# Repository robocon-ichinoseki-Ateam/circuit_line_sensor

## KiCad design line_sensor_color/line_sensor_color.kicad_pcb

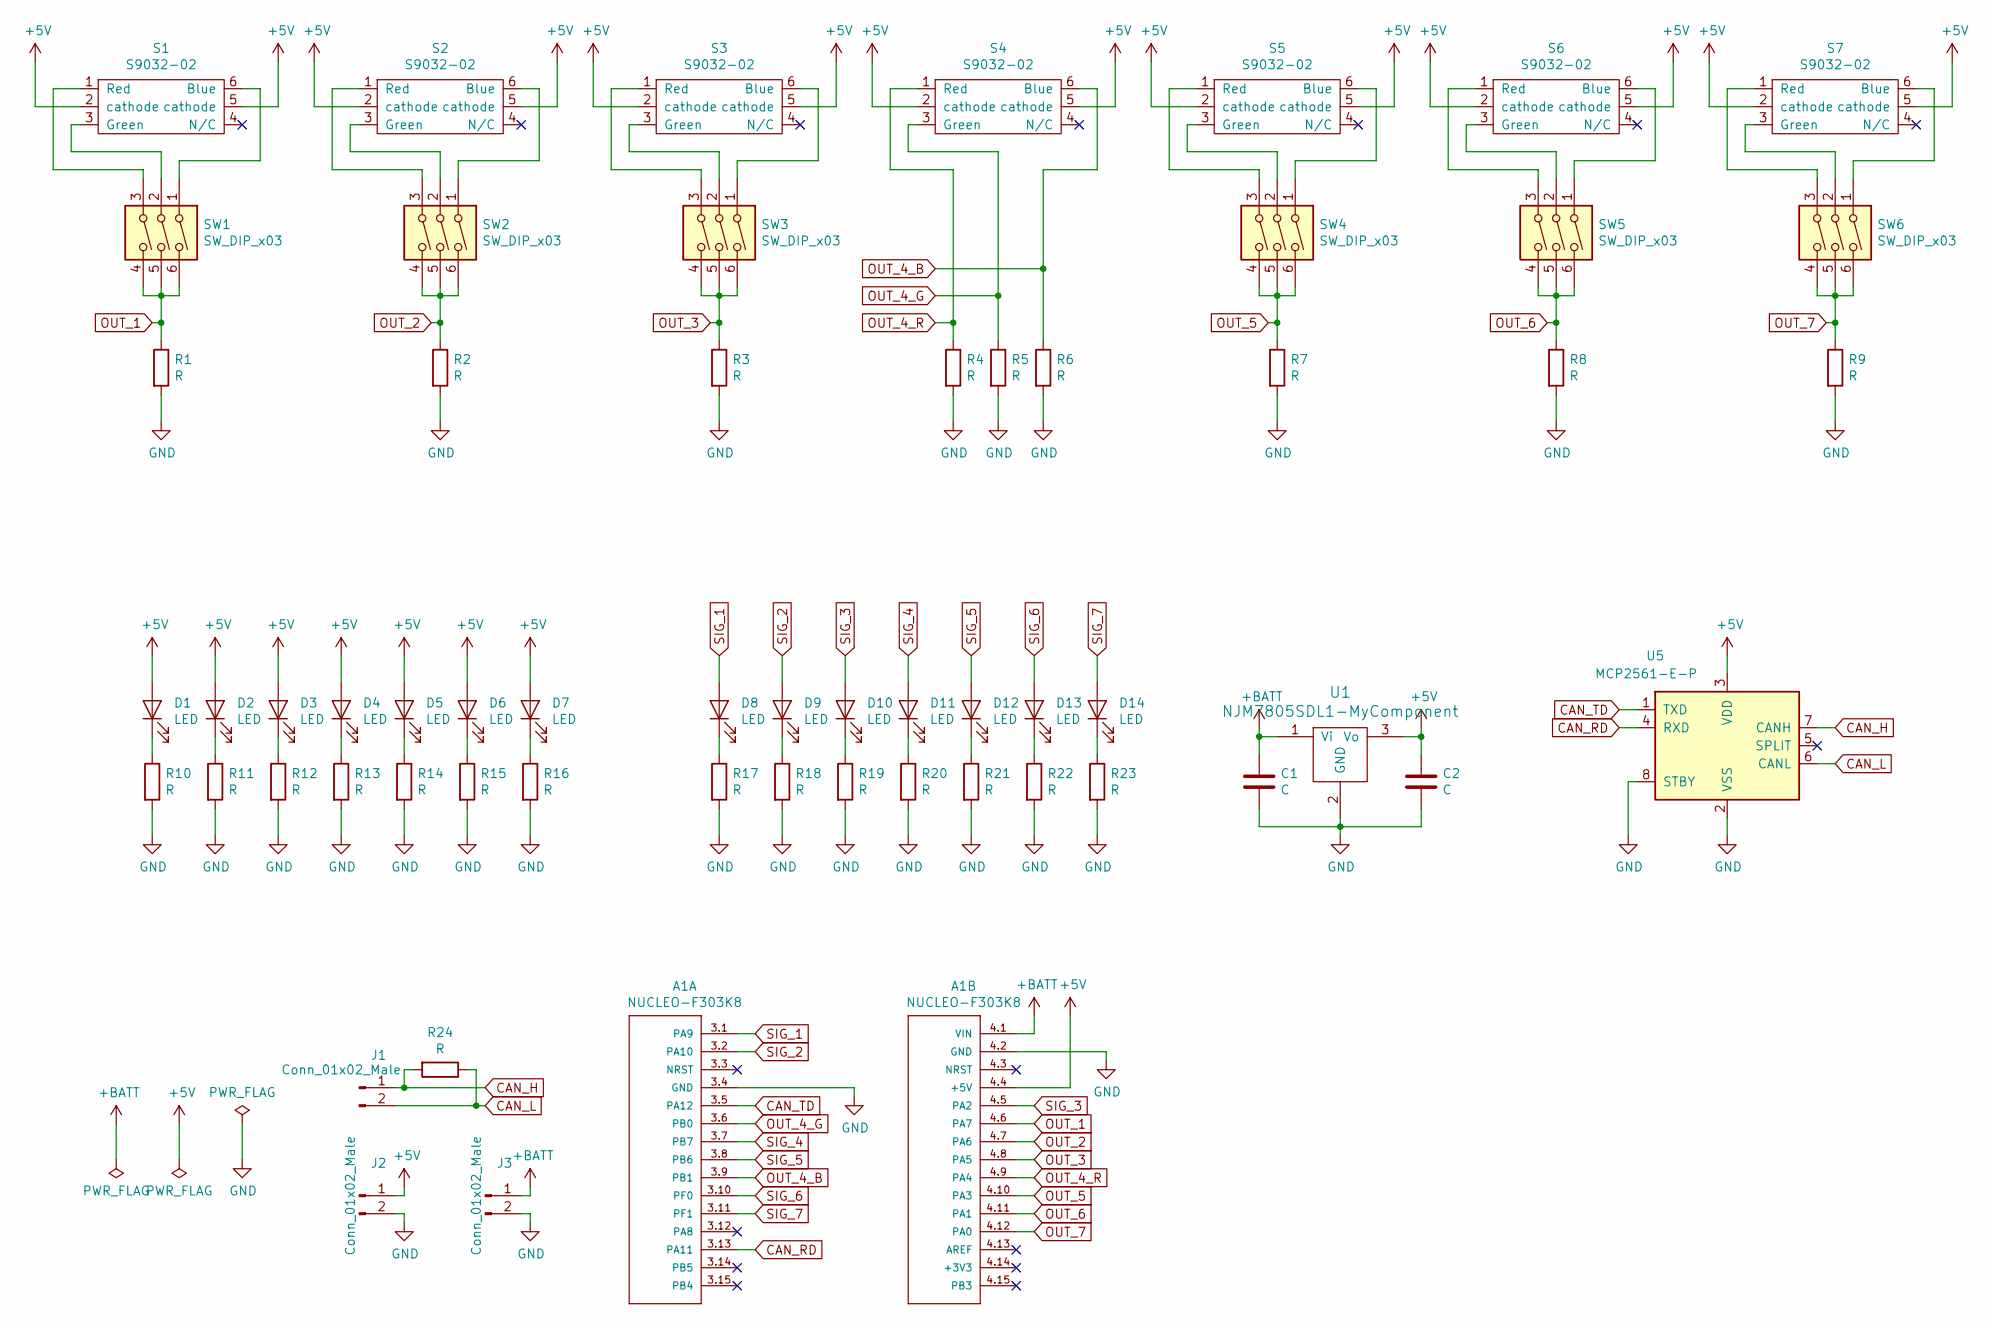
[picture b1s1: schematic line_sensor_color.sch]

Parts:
A1: NUCLEO-F303K8; NUCLEO_F303K8
C1, C2: C; C_0603_1608Metric_Pad1.05x0.95mm_HandSolder
D1, D2, D3, D4, D5, D6, D7: LED; OSW5DLS1C1A
D8, D9, D10, D11, D12, D13, D14: LED; LED_0603_1608Metric_Pad1.05x0.95mm_HandSolder
J1, J2, J3: Conn_01x02_Male; JST_XH_S2B-XH-A_1x02_P2.50mm_Horizontal
R1, R2, R3, R4, R5, R6, R7, R8, R9, R10, R11, R12, R13, R14, R15, R16, R24: R; R_Axial_DIN0207_L6.3mm_D2.5mm_P7.62mm_Horizontal
R17, R18, R19, R20, R21, R22, R23: R; R_0603_1608Metric_Pad1.05x0.95mm_HandSolder
S1, S2, S3, S4, S5, S6, S7: S9032-02
SW1, SW2, SW3, SW4, SW5, SW6: SW_DIP_x03; SW_DIP_SPSTx03_Slide_6.7x9.18mm_W7.62mm_P2.54mm_LowProfile
U1: NJM7805SDL1-MyComponent; TO-252-3_TabPin2
U5: MCP2561-E-P; DIP-8_W7.62mm

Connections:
+5V: A1.4.4 (+5V), C2.1, D1.2 (A), D2.2 (A), D3.2 (A), D4.2 (A), D5.2 (A), D6.2 (A), D7.2 (A), J2.1, S1.2 (cathode), S1.5 (cathode), S2.2 (cathode), S2.5 (cathode), S3.2 (cathode), S3.5 (cathode), S4.2 (cathode), S4.5 (cathode), S5.2 (cathode), S5.5 (cathode), S6.2 (cathode), S6.5 (cathode), S7.2 (cathode), S7.5 (cathode), U1.3 (Vo), U5.3 (VDD)
+BATT: A1.4.1 (VIN), C1.1, J3.1, U1.1 (Vi)
CAN_H: J1.1, R24.2, U5.7 (CANH)
CAN_L: J1.2, R24.1, U5.6 (CANL)
CAN_RD: A1.3.13 (PA11), U5.4 (RXD)
CAN_TD: A1.3.5 (PA12), U5.1 (TXD)
GND: A1.3.4 (GND), A1.4.2 (GND), C1.2, C2.2, J2.2, J3.2, R1.2, R2.2, R3.2, R4.2, R5.2, R6.2, R7.2, R8.2, R9.2, R10.2, R11.2, R12.2, R13.2, R14.2, R15.2, R16.2, R17.2, R18.2, R19.2, R20.2, R21.2, R22.2, R23.2, U1.2 (GND), U5.2 (VSS), U5.8 (STBY)
unnamed: D1.1 (K), R10.1
unnamed: D2.1 (K), R11.1
unnamed: D3.1 (K), R12.1
unnamed: D4.1 (K), R13.1
unnamed: D5.1 (K), R14.1
unnamed: D6.1 (K), R15.1
unnamed: D7.1 (K), R16.1
unnamed: D8.1 (K), R17.1
unnamed: D9.1 (K), R18.1
unnamed: D10.1 (K), R19.1
unnamed: D11.1 (K), R20.1
unnamed: D12.1 (K), R21.1
unnamed: D13.1 (K), R22.1
unnamed: D14.1 (K), R23.1
unnamed: S1.1 (Red), SW1.3
unnamed: S1.3 (Green), SW1.2
unnamed: S1.6 (Blue), SW1.1
unnamed: S2.1 (Red), SW2.3
unnamed: S2.3 (Green), SW2.2
unnamed: S2.6 (Blue), SW2.1
unnamed: S3.1 (Red), SW3.3
unnamed: S3.3 (Green), SW3.2
unnamed: S3.6 (Blue), SW3.1
unnamed: S5.1 (Red), SW4.3
unnamed: S5.3 (Green), SW4.2
unnamed: S5.6 (Blue), SW4.1
unnamed: S6.1 (Red), SW5.3
unnamed: S6.3 (Green), SW5.2
unnamed: S6.6 (Blue), SW5.1
unnamed: S7.1 (Red), SW6.3
unnamed: S7.3 (Green), SW6.2
unnamed: S7.6 (Blue), SW6.1
OUT_1: A1.4.6 (PA7), R1.1, SW1.4, SW1.5, SW1.6
OUT_2: A1.4.7 (PA6), R2.1, SW2.4, SW2.5, SW2.6
OUT_3: A1.4.8 (PA5), R3.1, SW3.4, SW3.5, SW3.6
OUT_4_B: A1.3.9 (PB1), R6.1, S4.6 (Blue)
OUT_4_G: A1.3.6 (PB0), R5.1, S4.3 (Green)
OUT_4_R: A1.4.9 (PA4), R4.1, S4.1 (Red)
OUT_5: A1.4.10 (PA3), R7.1, SW4.4, SW4.5, SW4.6
OUT_6: A1.4.11 (PA1), R8.1, SW5.4, SW5.5, SW5.6
OUT_7: A1.4.12 (PA0), R9.1, SW6.4, SW6.5, SW6.6
SIG_1: A1.3.1 (PA9), D8.2 (A)
SIG_2: A1.3.2 (PA10), D9.2 (A)
SIG_3: A1.4.5 (PA2), D10.2 (A)
SIG_4: A1.3.7 (PB7), D11.2 (A)
SIG_5: A1.3.8 (PB6), D12.2 (A)
SIG_6: A1.3.10 (PF0), D13.2 (A)
SIG_7: A1.3.11 (PF1), D14.2 (A)

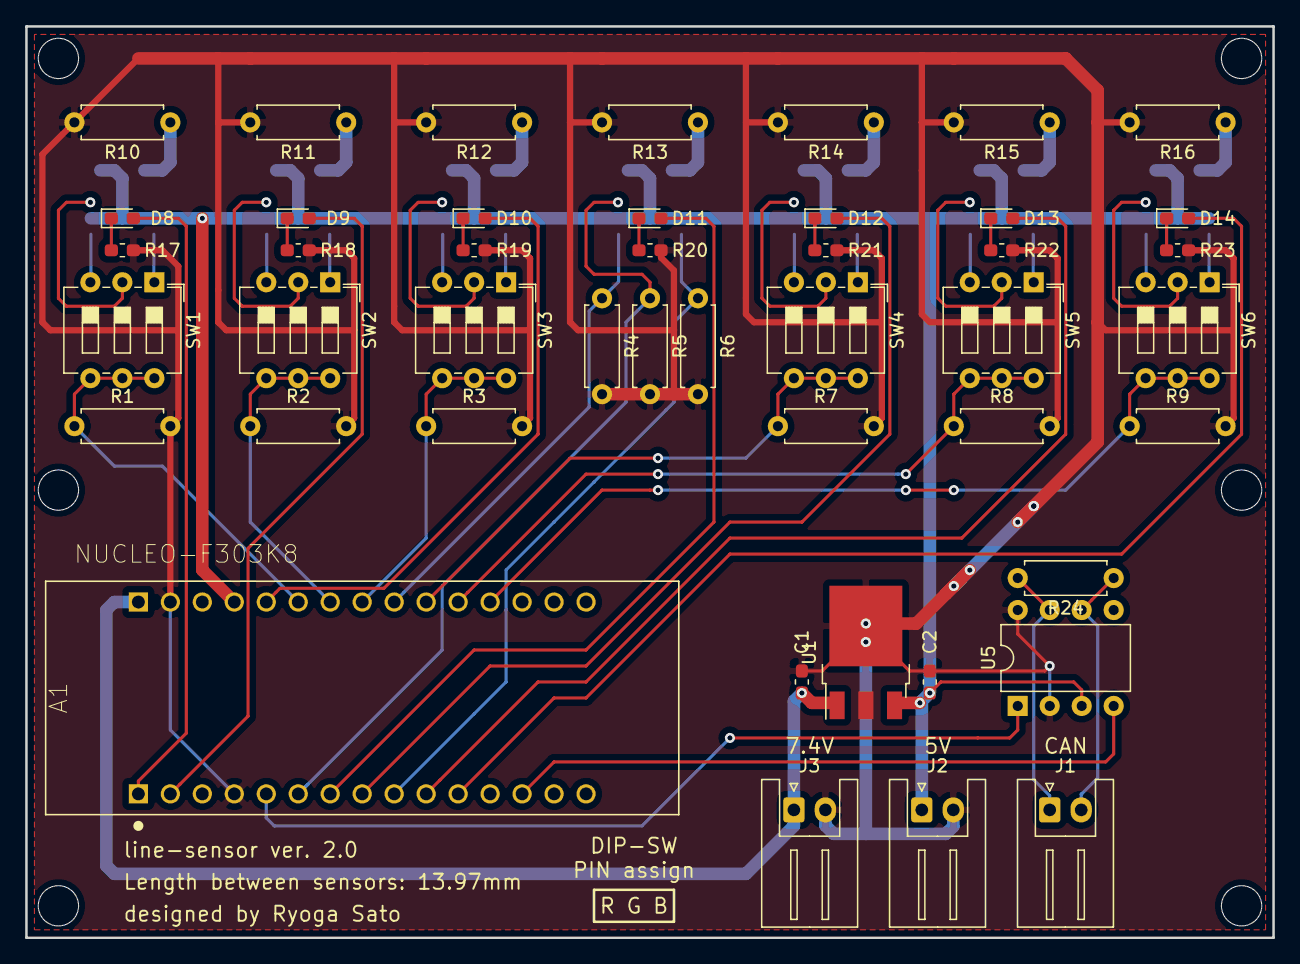
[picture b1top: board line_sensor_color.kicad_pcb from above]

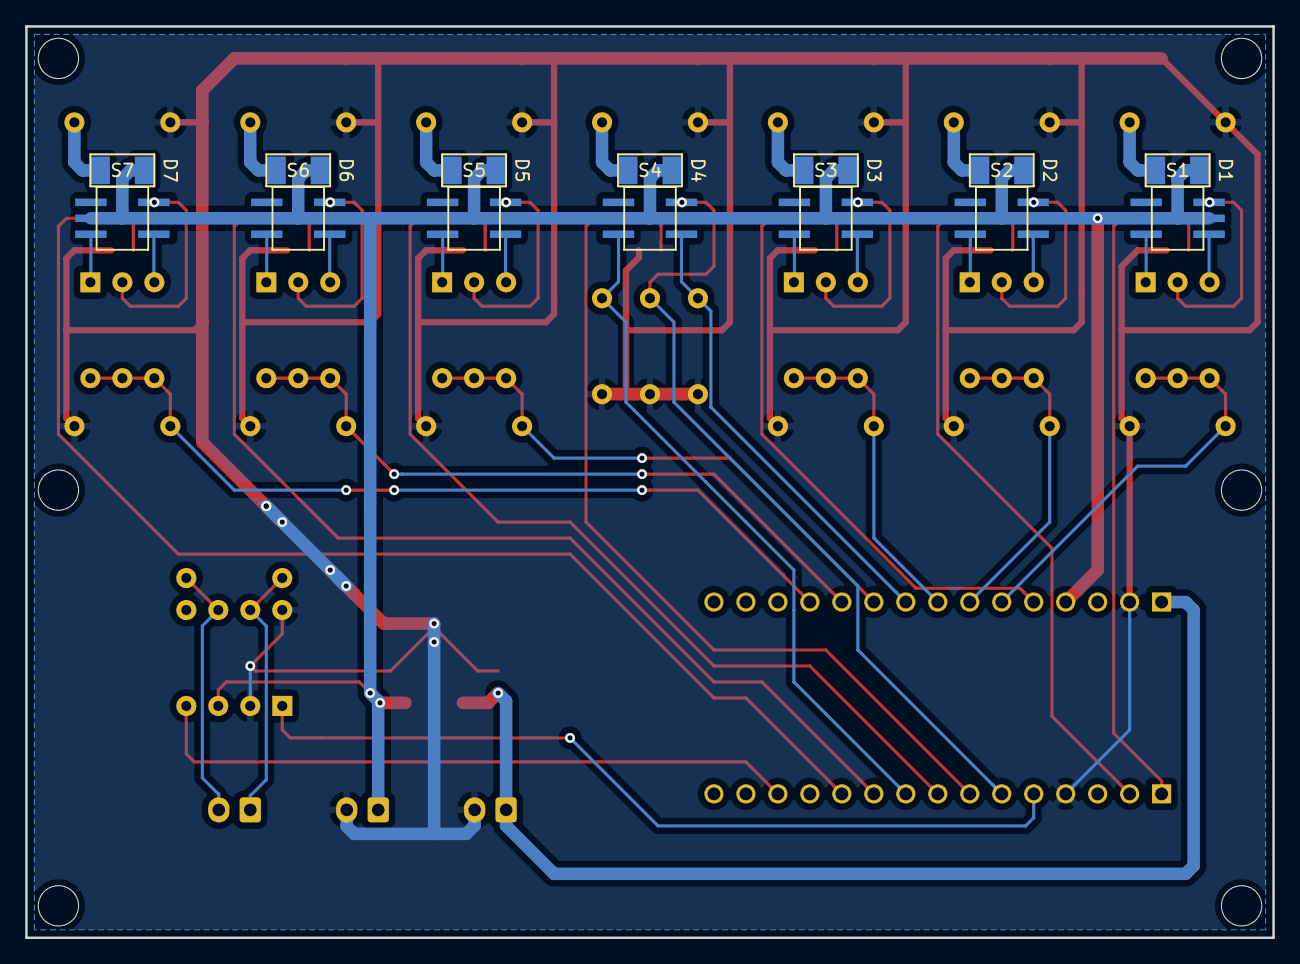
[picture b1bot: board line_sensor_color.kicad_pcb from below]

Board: 2 copper layers, 99.1 x 72.4 mm, 59 parts (14 on the bottom side), 55 nets.

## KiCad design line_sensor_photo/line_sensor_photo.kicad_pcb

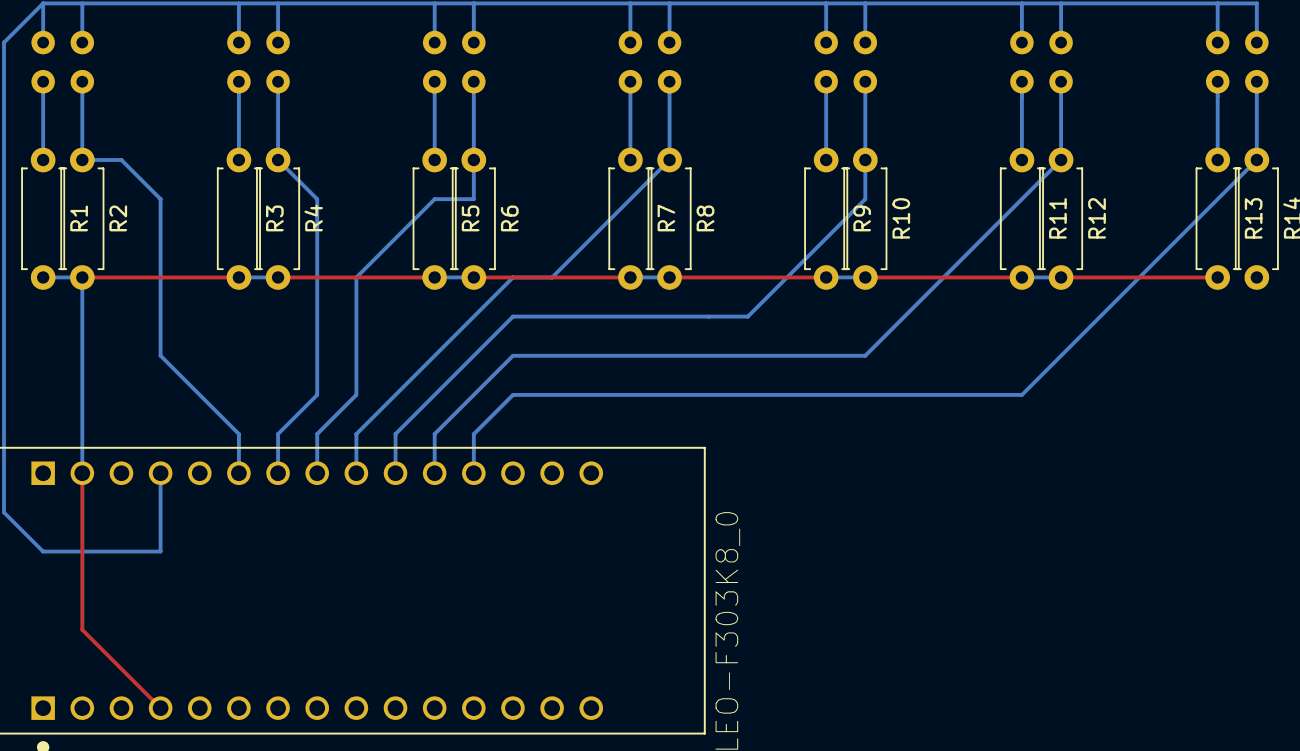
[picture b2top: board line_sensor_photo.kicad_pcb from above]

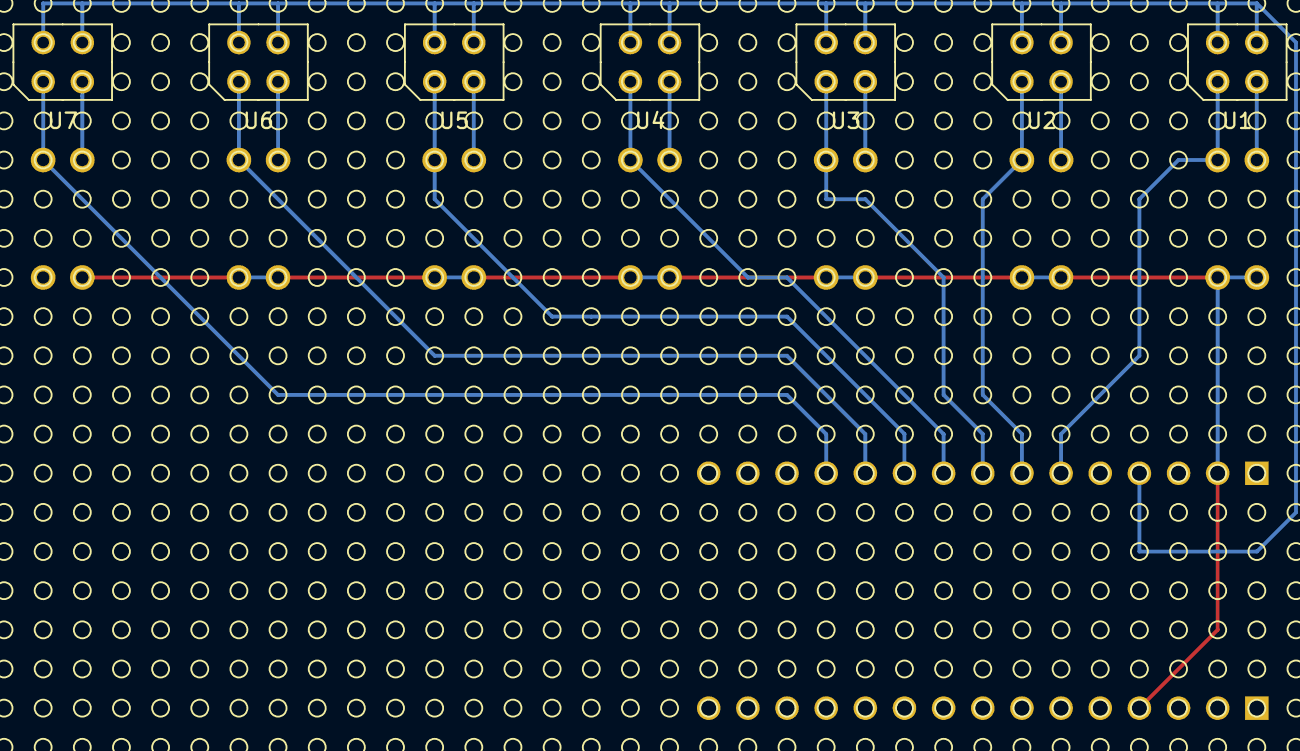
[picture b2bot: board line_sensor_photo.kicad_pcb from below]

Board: 2 copper layers, 22 parts (7 on the bottom side), 16 nets.

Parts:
A1: NUCLEO-F303K8_0; NUCLEO_F303K8
R1, R2, R3, R4, R5, R6, R7, R8, R9, R10, R11, R12, R13, R14: R; R_Axial_DIN0207_L6.3mm_D2.5mm_P7.62mm_Horizontal
U1, U2, U3, U4, U5, U6, U7: RPR-220

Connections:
+5V: A1.4.4, U1.1, U1.4, U2.1, U2.4, U3.1, U3.4, U4.1, U4.4, U5.1, U5.4, U6.1, U6.4, U7.1, U7.4
GND: A1.3.4, A1.4.2, R1.2, R2.2, R3.2, R4.2, R5.2, R6.2, R7.2, R8.2, R9.2, R10.2, R11.2, R12.2, R13.2, R14.2
unnamed: R1.1, U1.2
unnamed: R3.1, U2.2
unnamed: R5.1, U3.2
unnamed: R7.1, U4.2
unnamed: R9.1, U5.2
unnamed: R11.1, U6.2
unnamed: R13.1, U7.2
OUT_1: A1.4.6, R2.1, U1.3
OUT_2: A1.4.7, R4.1, U2.3
OUT_3: A1.4.8, R6.1, U3.3
OUT_4: A1.4.9, R8.1, U4.3
OUT_5: A1.4.10, R10.1, U5.3
OUT_6: A1.4.11, R12.1, U6.3
OUT_7: A1.4.12, R14.1, U7.3

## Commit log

2019-04-27 update: 回路図設計，フットプリントの関連付け
2019-04-27 update: ネットリストを吐いた
2019-04-28 update: ver.2.0 設計終了
2019-06-27 update: ライブラリ関係を統合，リネーム
2019-06-27 update: ライブラリの更新
2019-06-28 update: ver.1.0 設計終了
2019-06-28 rename: ラインセンサのディレクトリを分けた
2019-06-28 update: フォトリフレクタ型のラインセンサを設計
2019-07-09 update: フットプリントに3Dデータを追加
2019-07-10 fix: ライブラリのバグを修正
